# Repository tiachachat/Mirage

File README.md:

# Mirage
# ESP32-C3 Wi-Fi Device Controller

## Overview
This project is designed to control devices through Wi-Fi using the ESP32-C3 microcontroller. The project includes both the hardware design (PCB) and the software (firmware) to enable Wi-Fi-based control of various devices.

## Features
- **Wi-Fi Connectivity**: Connect and control devices over a Wi-Fi network.
- **Web Interface**: Simple web-based interface for device control.
- **Open Source**: Both hardware and software are open-source.

## 3D view Rendring

## Photo

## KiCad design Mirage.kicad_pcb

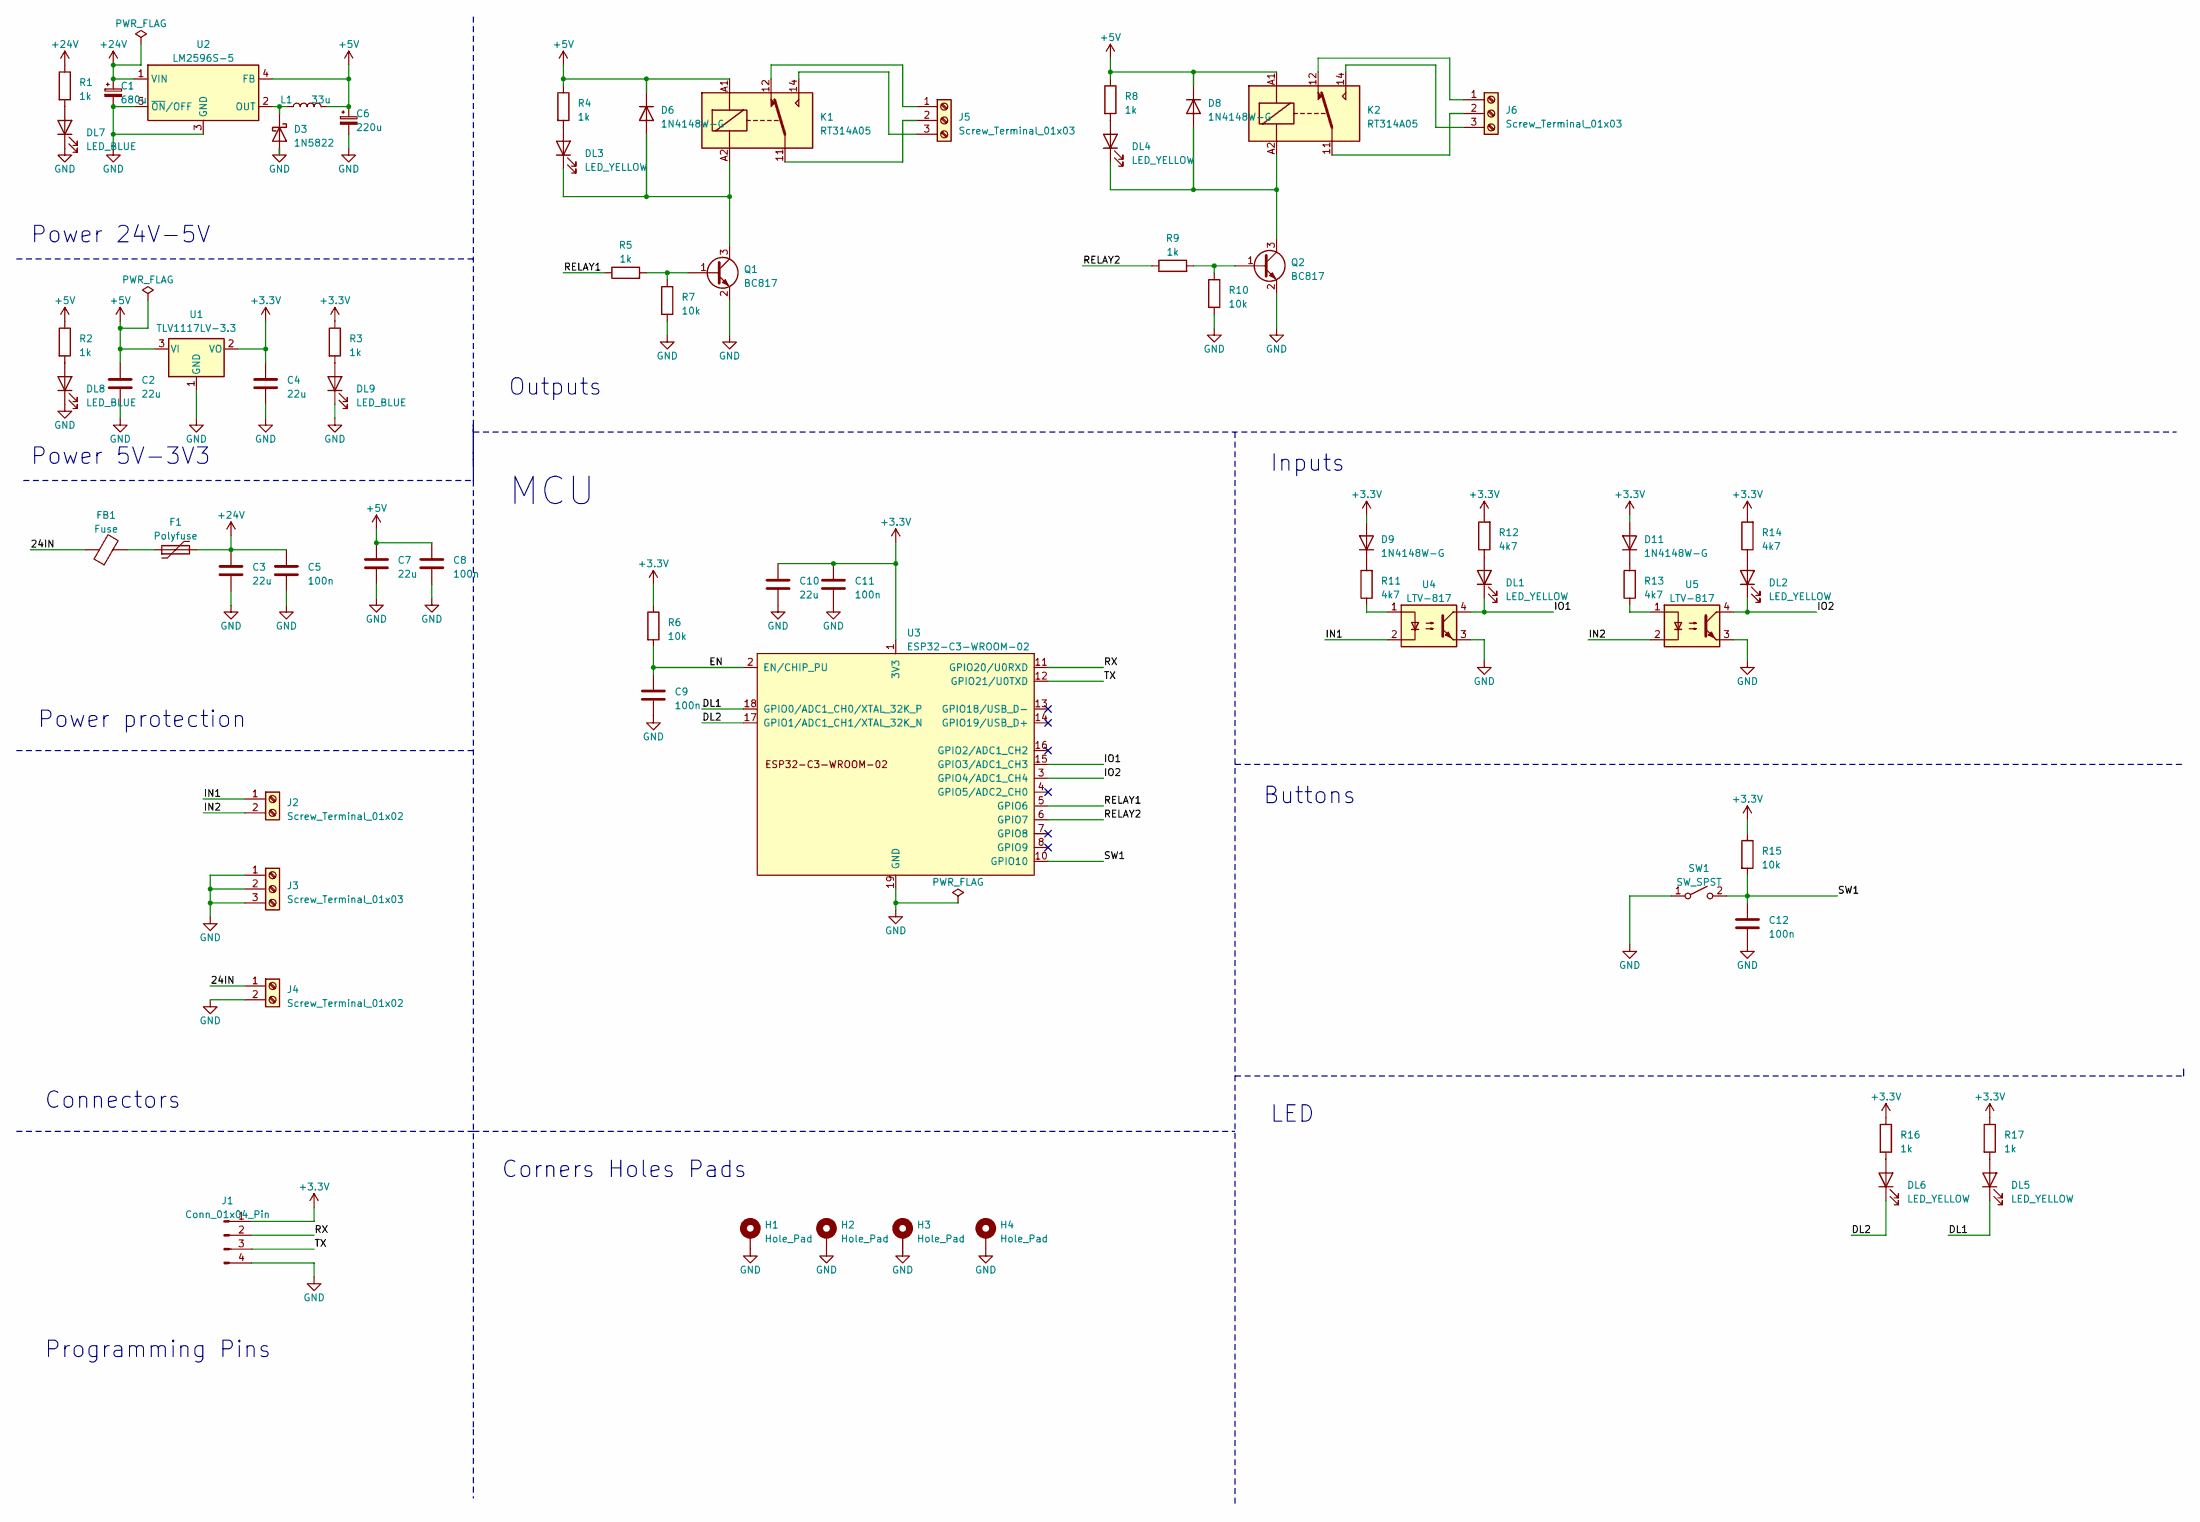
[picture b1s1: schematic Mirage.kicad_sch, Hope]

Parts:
C1: 680u; CP_Radial_D12.5mm_P5.00mm
C2, C3, C4, C7, C10: 22u; C_1206_3216Metric_Pad1.33x1.80mm_HandSolder
C5, C8, C9, C11, C12: 100n; C_Disc_D7.0mm_W2.5mm_P5.00mm
C6: 220u; CP_Radial_D12.5mm_P5.00mm
D3: 1N5822; D_DO-201AD_P5.08mm_Vertical_AnodeUp
D6, D8, D9, D11: 1N4148W-G; D_SOD-123
DL1, DL2, DL3, DL4, DL5, DL6: LED_YELLOW; LED_1206_3216Metric_Pad1.42x1.75mm_HandSolder
DL7, DL8, DL9: LED_BLUE; LED_1206_3216Metric_Pad1.42x1.75mm_HandSolder
F1: Polyfuse; FX0321
FB1: Fuse; BLM21AG102BH1J
H1, H2, H3, H4: Hole_Pad; MountingHole_3.2mm_M3_Pad_Via
J1: Conn_01x04_Pin; PinHeader_1x04_P2.54mm_Vertical
J2, J4: Screw_Terminal_01x02; TerminalBlock_Phoenix_MKDS-1,5-2-5.08_1x02_P5.08mm_Horizont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
J3, J5, J6: Screw_Terminal_01x03; TerminalBlock_Phoenix_MKDS-3-3-5.08_1x03_P5.08mm_Horizontal
K1, K2: RT314A05; Relay_SPDT_Schrack-RT1-16A-FormC_RM5mm
L1: 33u; L_Radial_D8.7mm_P5.00mm_Fastron_07HCP
Q1, Q2: BC817; SOT-23
R1, R2, R3, R4, R5, R8, R9, R16, R17: 1k; R_1206_3216Metric_Pad1.30x1.75mm_HandSolder
R6, R7, R10, R15: 10k; R_1206_3216Metric_Pad1.30x1.75mm_HandSolder
R11, R12, R13, R14: 4k7; R_1206_3216Metric_Pad1.30x1.75mm_HandSolder
SW1: SW_SPST; SW_PUSH_6mm_H5mm
U1: TLV1117LV-3.3; SOT-223-3_TabPin2
U2: LM2596S-5; TO-263-5_TabPin3
U3: ESP32-C3-WROOM-02; ESP32-C3-WROOM-02U
U4, U5: LTV-817; DIP-4_W7.62mm

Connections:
+3.3V: C4.1, C10.1, C11.1, D9.2 (A), D11.2 (A), J1.1, R3.1, R6.1, R12.2, R14.2, R15.1, R16.1, R17.1, U1.2 (VO), U3.1 (3V3)
+5V: C2.1, C6.1, C7.1, C8.1, D6.1 (K), D8.1 (K), K1.A1, K2.A1, L1.2, R2.1, R4.1, R8.1, U1.3 (VI), U2.4 (FB)
+24V: C1.1, C3.1, C5.1, F1.2, R1.1, U2.1 (VIN)
/24IN: FB1.1, J4.1
/DL1: DL5.1 (K), U3.18 (GPIO0/ADC1_CH0/XTAL_32K_P)
/DL2: DL6.1 (K), U3.17 (GPIO1/ADC1_CH1/XTAL_32K_N)
/EN: C9.1, R6.2, U3.2 (EN/CHIP_PU)
/IN1: J2.1, U4.2
/IN2: J2.2, U5.2
/IO1: DL1.1 (K), U3.15 (GPIO3/ADC1_CH3), U4.4
/IO2: DL2.1 (K), U3.3 (GPIO4/ADC1_CH4), U5.4
/RELAY1: R5.1, U3.5 (GPIO6)
/RELAY2: R9.1, U3.6 (GPIO7)
/RX: J1.2, U3.11 (GPIO20/U0RXD)
/SW1: C12.1, R15.2, SW1.2 (B), U3.10 (GPIO10)
/TX: J1.3, U3.12 (GPIO21/U0TXD)
GND: C1.2, C2.2, C3.2, C4.2, C5.2, C6.2, C7.2, C8.2, C9.2, C10.2, C11.2, C12.2, D3.2 (A), DL7.1 (K), DL8.1 (K), DL9.1 (K), H1.1, H2.1, H3.1, H4.1, J1.4, J3.1, J3.2, J3.3, J4.2, Q1.2 (E), Q2.2 (E), R7.2, R10.2, SW1.1 (A), U1.1 (GND), U2.3 (GND), U2.5 (~ON/OFF), U3.9 (GND), U3.19 (GND), U4.3, U5.3
unnamed: D3.1 (K), L1.1, U2.2 (OUT)
unnamed: D6.2 (A), DL3.1 (K), K1.A2, Q1.3 (C)
unnamed: D8.2 (A), DL4.1 (K), K2.A2, Q2.3 (C)
unnamed: D9.1 (K), R11.2
unnamed: D11.1 (K), R13.2
unnamed: DL1.2 (A), R12.1
unnamed: DL2.2 (A), R14.1
unnamed: DL3.2 (A), R4.2
unnamed: DL4.2 (A), R8.2
unnamed: DL5.2 (A), R17.2
unnamed: DL6.2 (A), R16.2
unnamed: DL7.2 (A), R1.2
unnamed: DL8.2 (A), R2.2
unnamed: DL9.2 (A), R3.2
unnamed: F1.1, FB1.2
unnamed: J5.1, K1.12
unnamed: J5.2, K1.11
unnamed: J5.3, K1.14
unnamed: J6.1, K2.12
unnamed: J6.2, K2.11
unnamed: J6.3, K2.14
unnamed: Q1.1 (B), R5.2, R7.1
unnamed: Q2.1 (B), R9.2, R10.1
unnamed: R11.1, U4.1
unnamed: R13.1, U5.1

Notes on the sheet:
Outputs
Inputs
Corners Holes Pads
Power protection
Power 5V-3V3
LED
Programming Pins
MCU
Buttons
Power 24V-5V
Connectors

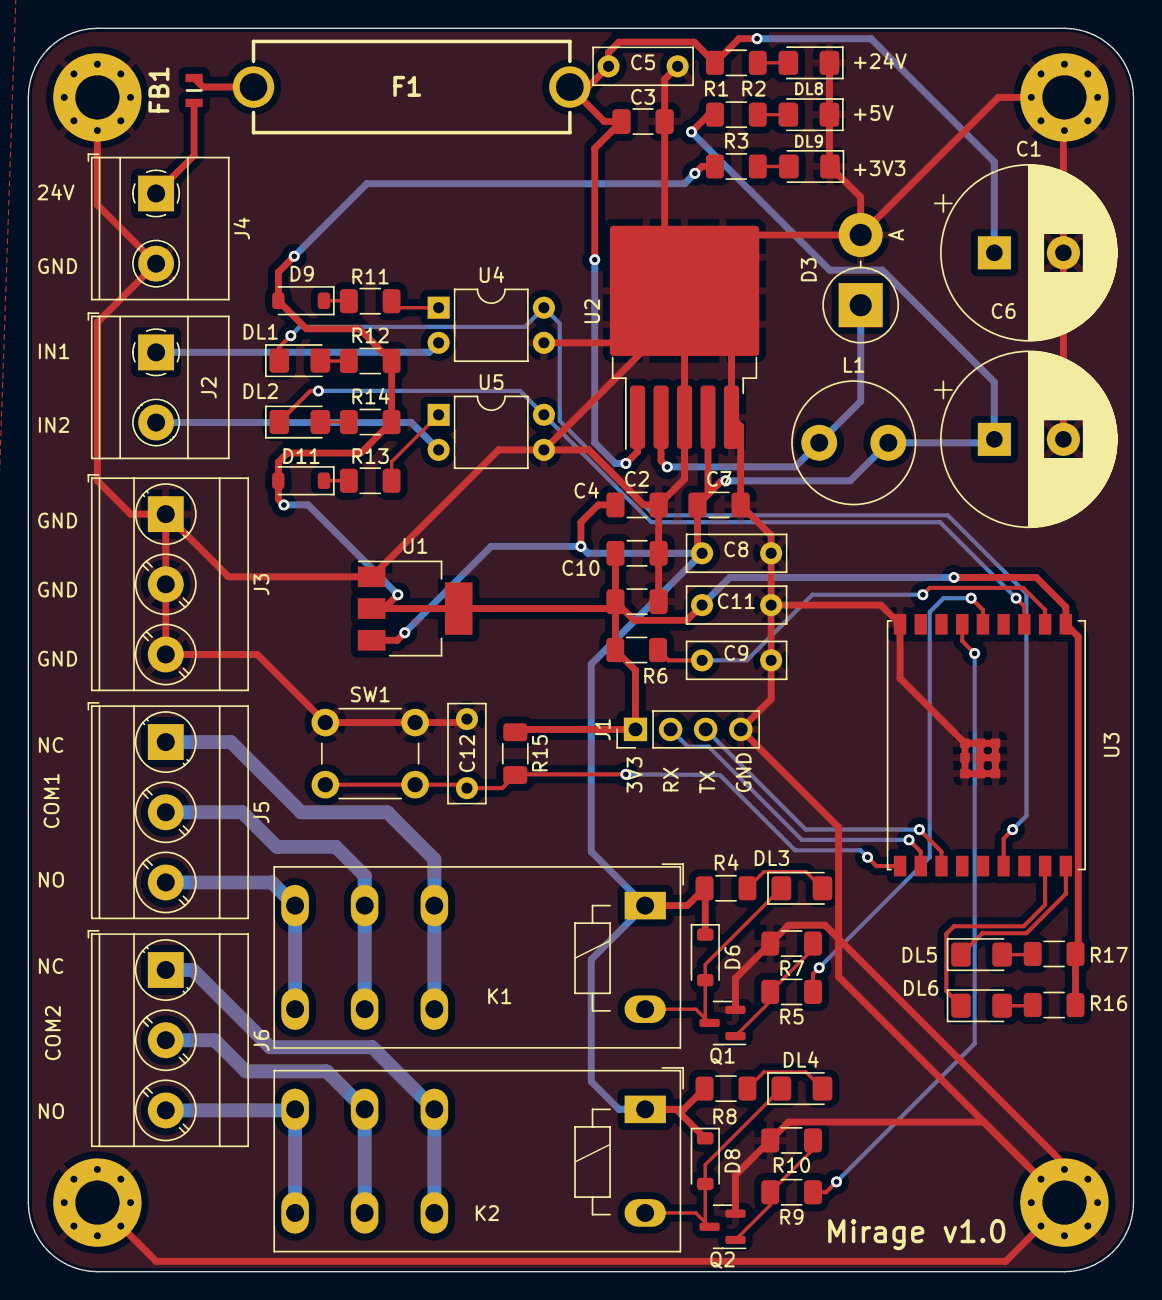
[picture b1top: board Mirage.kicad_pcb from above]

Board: 2 copper layers, 80.0 x 90.0 mm, 66 parts (0 on the bottom side), 42 nets.

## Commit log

2024-07-23 README.md
